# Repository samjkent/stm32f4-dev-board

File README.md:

# STM32 USB Development Board

A custom STM32 development board using an STM32F401RBT6 with footprints for:

- LSE and HSE crystals
- USB-C or micro-USB connectors
- External power connector

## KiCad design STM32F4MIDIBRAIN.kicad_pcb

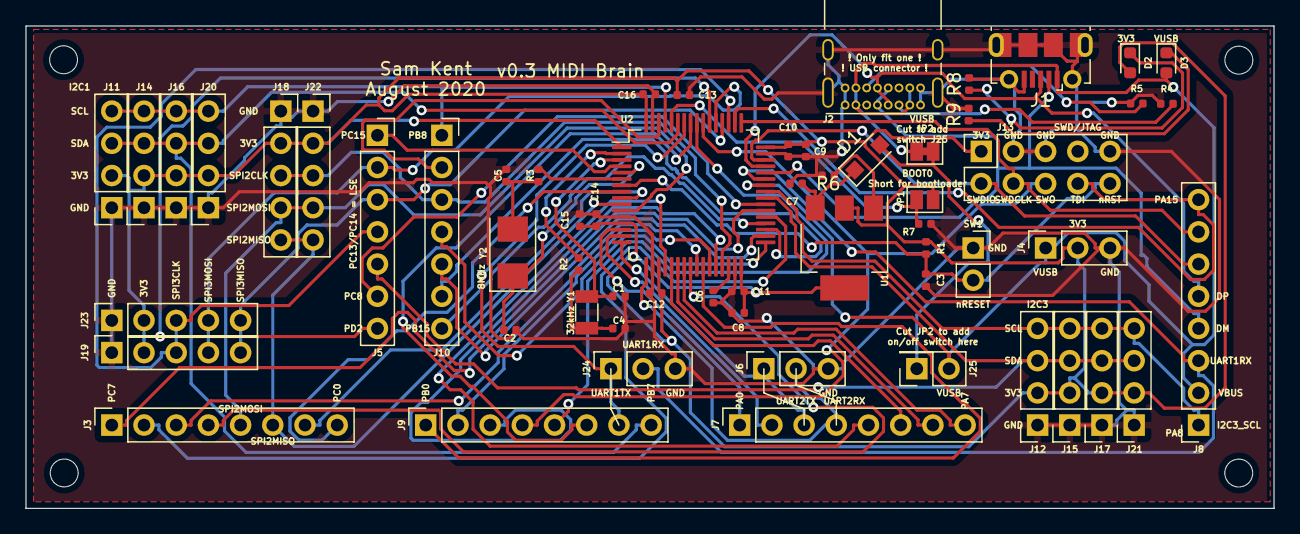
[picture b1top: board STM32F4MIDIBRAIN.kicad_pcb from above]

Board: 2 copper layers, 98.4 x 38.1 mm, 60 parts (0 on the bottom side), 64 nets.

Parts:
C1, C4: 12.5pF; C_0402_1005Metric
C2, C5: 20pF; C_0402_1005Metric
C3, C10, C11, C12, C13, C14, C15: 100nF; C_0402_1005Metric
C6: 4.7uF; C_0402_1005Metric
C7, C16: 1uF; C_0402_1005Metric
C8: 2.2uF; C_0402_1005Metric
C9: 10uF; C_0402_1005Metric
D1: D; D_SOD-123F
D2, D3: LED; LED_0603_1608Metric
J1: MicroUSB; USB_Micro-B_Molex-105017-0001
J2: USBC; USB_C_Receptacle_GCT_USB4085
J3: PORTC1; PinSocket_1x08_P2.54mm_Vertical
J4: POWER; PinSocket_1x03_P2.54mm_Vertical
J5: PORTC2; PinSocket_1x07_P2.54mm_Vertical
J6: UART2; PinSocket_1x03_P2.54mm_Vertical
J7: PORTA1; PinSocket_1x08_P2.54mm_Vertical
J8: PORTA2; PinSocket_1x08_P2.54mm_Vertical
J9: PORTB1; PinSocket_1x08_P2.54mm_Vertical
J10: PORTB2; PinSocket_1x07_P2.54mm_Vertical
J11: I2C1_1; PinSocket_1x04_P2.54mm_Vertical
J12: I2C3_1; PinSocket_1x04_P2.54mm_Vertical
J13: JTAG/SWD; PinSocket_2x05_P2.54mm_Vertical
J14: I2C1_2; PinSocket_1x04_P2.54mm_Vertical
J15: I2C3_2; PinSocket_1x04_P2.54mm_Vertical
J16: I2C1_3; PinSocket_1x04_P2.54mm_Vertical
J17: I2C3_3; PinSocket_1x04_P2.54mm_Vertical
J18: SPI2_1; PinSocket_1x05_P2.54mm_Vertical
J19: SPI3_1; PinSocket_1x05_P2.54mm_Vertical
J20: I2C1_4; PinSocket_1x04_P2.54mm_Vertical
J21: I2C3_4; PinSocket_1x04_P2.54mm_Vertical
J22: SPI2_2; PinSocket_1x05_P2.54mm_Vertical
J23: SPI3_2; PinSocket_1x05_P2.54mm_Vertical
J24: UART1; PinSocket_1x03_P2.54mm_Vertical
J25: VUSB_SWITCH; PinSocket_2x01_P2.54mm_Vertical
JP1: BOOT0; SolderJumper-2_P1.3mm_Open_Pad1.0x1.5mm
JP2: VUSB; SolderJumper-2_P1.3mm_Bridged_Pad1.0x1.5mm
R1, R7: 10K; R_0402_1005Metric
R2: 50KR; R_0402_1005Metric
R3: 1KR; R_0402_1005Metric
R4, R5: 5.11K; R_0402_1005Metric
R6: 332K; R_0402_1005Metric
R8, R9: 1K; R_0402_1005Metric
SW1: RESET; PinSocket_1x02_P2.54mm_Vertical
U1: AMS1117-3.3; SOT-223
U2: STM32F401RBTx; LQFP-64_10x10mm_P0.5mm
Y1: 32kHz; Crystal_SMD_3215-2Pin_3.2x1.5mm
Y2: 8MHz; Crystal_SMD_5032-2Pin_5.0x3.2mm

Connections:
+3V3: C8.1, C9.1, C10.1, C11.1, C12.1, C13.1, C14.1, C15.1, C16.1, D2.2, J4.2, J11.2, J12.2, J13.1, J14.2, J15.2, J16.2, J17.2, J18.2, J19.2, J20.2, J21.2, J22.2, J23.2, JP1.2, R1.1, U1.2, U1.4, U2.1, U2.13, U2.19, U2.32, U2.48, U2.64
/BOOT0: JP1.1, R7.1, U2.60
/DM: J1.2, J2.A7, J2.B7, J8.4, U2.44
/DP: J1.3, J2.A6, J2.B6, J8.5, U2.45
/HSE_IN: C2.2, U2.5, Y2.1
/HSE_OUT: R3.2, U2.6
/I2C1_SCL: J10.1, J11.4, J14.4, J16.4, J20.4, U2.61
/I2C1_SDA: J9.8, J11.3, J14.3, J16.3, J20.3, U2.59
/I2C3_SCL: J8.1, J12.4, J15.4, J17.4, J21.4, U2.41
/I2C3_SDA: J5.5, J12.3, J15.3, J17.3, J21.3, U2.40
/LSE_IN: C1.2, U2.3, Y1.1
/LSE_OUT: R2.2, U2.2
/PD2: J5.7, U2.54
/SPI2_CLK: J10.3, J18.3, J22.3, U2.29
/SPI2_MISO: J3.6, J18.5, J22.5, U2.10
/SPI2_MOSI: J3.5, J18.4, J22.4, U2.11
/SPI3_CLK: J5.4, J19.3, J23.3, U2.51
/SPI3_MISO: J5.3, J19.5, J23.5, U2.52
/SPI3_MOSI: J5.2, J19.4, J23.4, U2.53
/SWDCLK: J8.7, J13.4, U2.49
/SWDIO: J8.6, J13.2, U2.46
/SWO: J9.4, J13.6, U2.55
/TDI: J8.8, J13.8, U2.50
/UART1_RX: J8.3, J24.2, U2.43
/UART1_TX: J9.7, J24.1, U2.58
/UART_RX: J6.2, J7.4, U2.17
/UART_TX: J6.1, J7.3, U2.16
/VUSB: D3.2, J1.1, J2.A4, J2.A9, J2.B4, J2.B9, J4.1, J8.2, J25.2, JP2.1, U2.42
/nRST: C3.1, J13.10, R1.2, SW1.2, U2.7
GND: C1.1, C2.1, C3.2, C4.2, C5.2, C6.2, C7.2, C8.2, C9.2, C10.2, C11.2, C12.2, C13.2, C14.2, C15.2, C16.2, J1.5, J1.6, J2.A1, J2.A12, J2.B1, J2.B12, J2.S1, J4.3, J6.3, J11.1, J12.1, J13.3, J13.5, J13.9, J14.1, J15.1, J16.1, J17.1, J18.1, J19.1, J20.1, J21.1, J22.1, J23.1, J24.3, R4.1, R5.1, R6.2, R7.2, R8.2, R9.2, SW1.1, U2.12, U2.18, U2.31, U2.47, U2.63
unnamed: C4.1, R2.1, Y1.2
unnamed: C5.1, R3.1, Y2.2
unnamed: C6.1, U2.30
unnamed: C7.1, D1.1, U1.3
unnamed: D1.2, J25.1, JP2.2
unnamed: D2.1, R8.1
unnamed: D3.1, R9.1
unnamed: J2.A5, R4.2
unnamed: J2.B5, R5.2
unnamed: J3.1, U2.38
unnamed: J3.2, U2.37
unnamed: J3.3, U2.25
unnamed: J3.4, U2.24
unnamed: J3.7, U2.9
unnamed: J3.8, U2.8
unnamed: J5.1, U2.4
unnamed: J5.6, U2.39
unnamed: J7.1, U2.14
unnamed: J7.2, U2.15
unnamed: J7.5, U2.20
unnamed: J7.6, U2.21
unnamed: J7.7, U2.22
unnamed: J7.8, U2.23
unnamed: J9.1, U2.26
unnamed: J9.2, U2.27
unnamed: J9.3, U2.28
unnamed: J9.5, U2.56
unnamed: J9.6, U2.57
unnamed: J10.2, U2.62
unnamed: J10.4, U2.33
unnamed: J10.5, U2.34
unnamed: J10.6, U2.35
unnamed: J10.7, U2.36
unnamed: R6.1, U1.1

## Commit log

2021-01-12 add image
